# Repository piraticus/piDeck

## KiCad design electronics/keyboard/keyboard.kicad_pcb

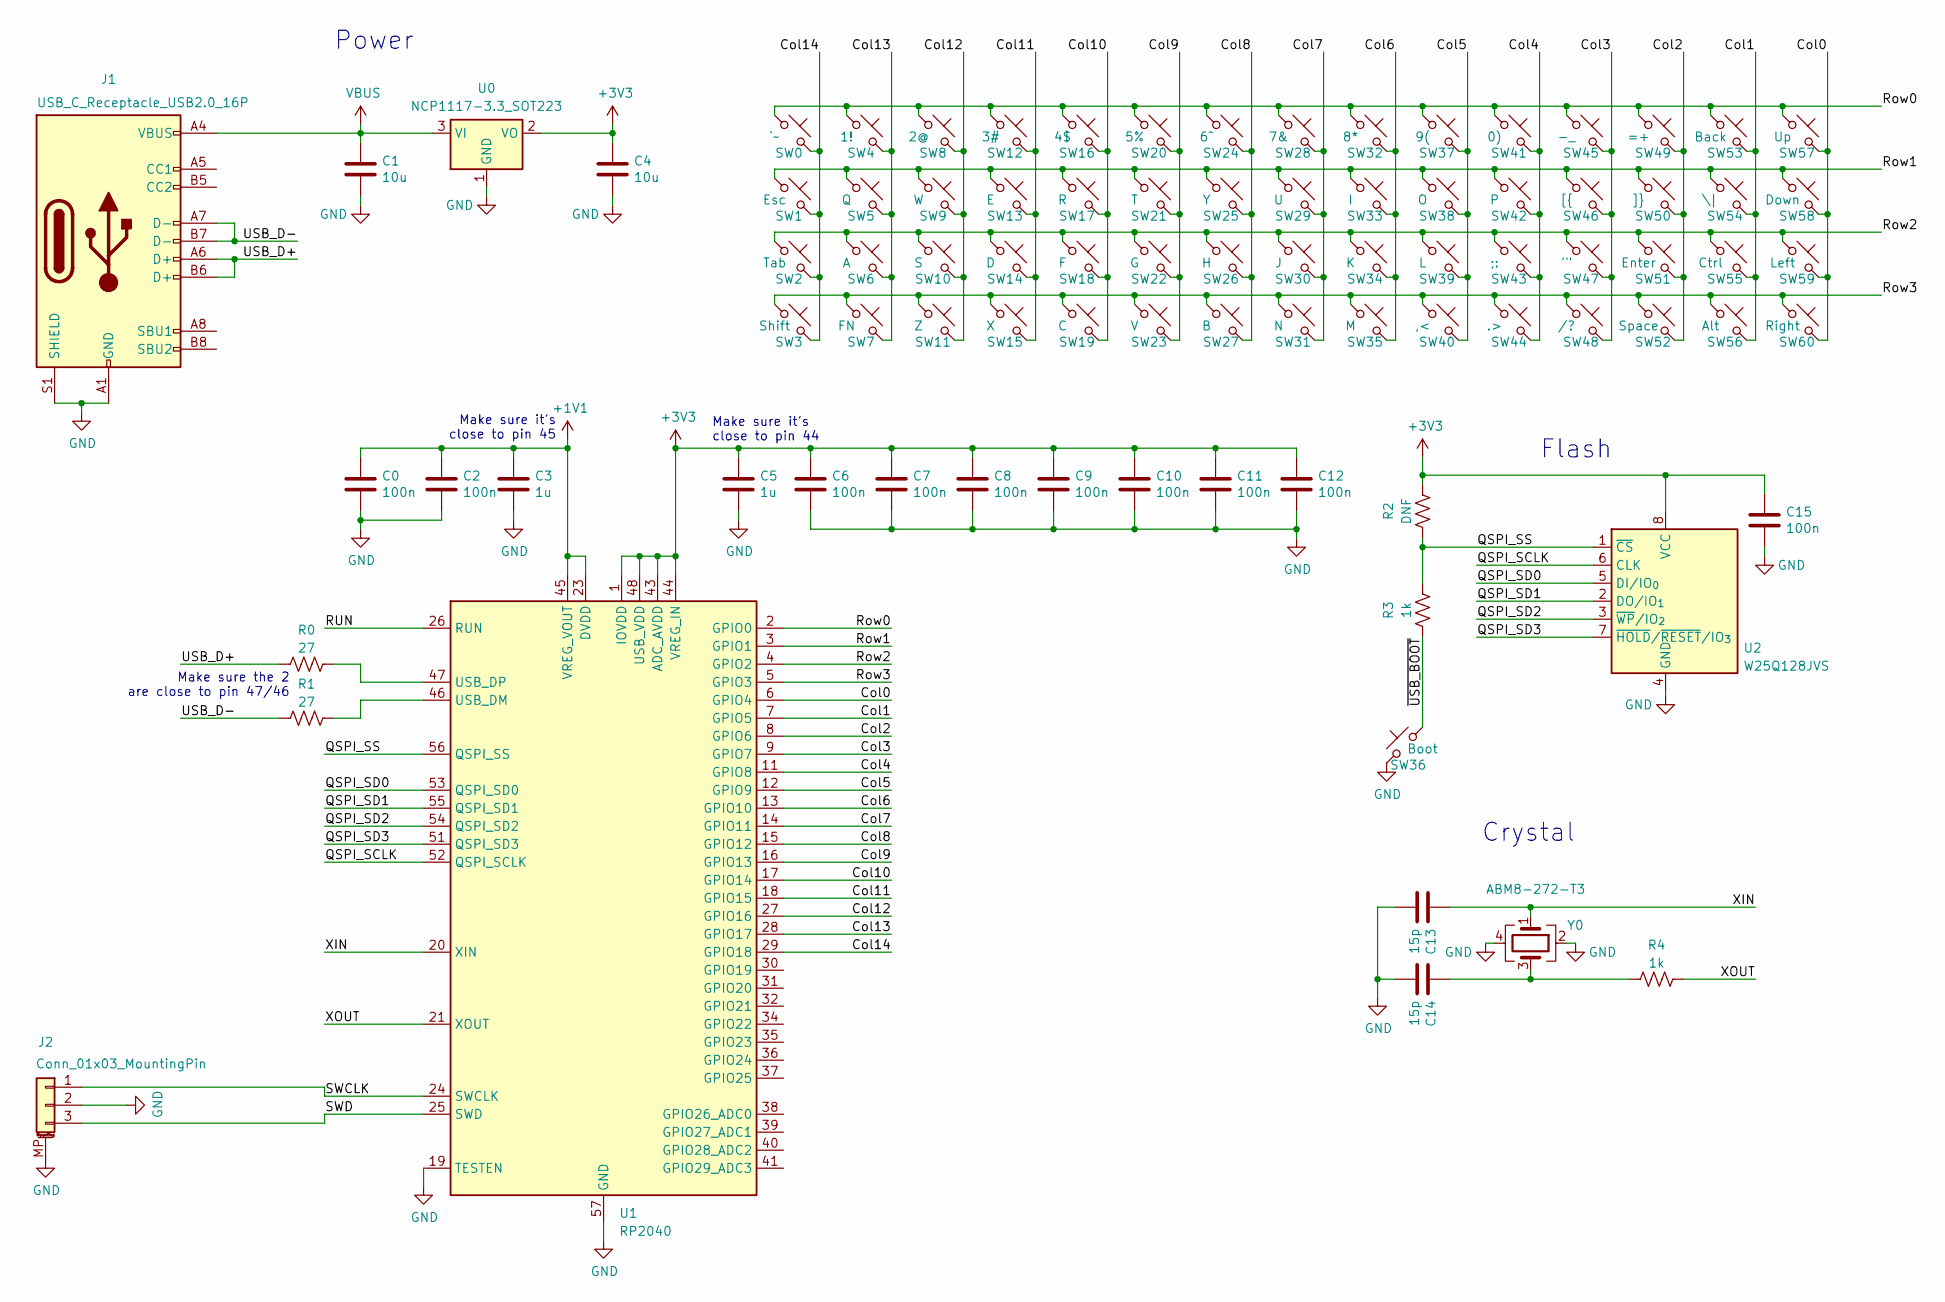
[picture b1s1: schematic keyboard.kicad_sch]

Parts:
C0, C2, C6, C7, C8, C9, C10, C11, C12, C15: 100n; C_0603_1608Metric_Pad1.08x0.95mm_HandSolder
C1, C4: 10u; C_0805_2012Metric_Pad1.18x1.45mm_HandSolder
C3, C5: 1u; C_0603_1608Metric_Pad1.08x0.95mm_HandSolder
C13, C14: 15p; C_0402_1005Metric_Pad0.74x0.62mm_HandSolder
J1: USB_C_Receptacle_USB2.0_16P; USB_C_Receptacle_GCT_USB4085
J2: Conn_01x03_MountingPin; JST_SH_SM03B-SRSS-TB_1x03-1MP_P1.00mm_Horizontal
R0, R1: 27; R_0603_1608Metric_Pad0.98x0.95mm_HandSolder
R2: DNF; R_0603_1608Metric_Pad0.98x0.95mm_HandSolder
R3, R4: 1k; R_0603_1608Metric_Pad0.98x0.95mm_HandSolder
SW0: `~; SW_PUSH_6mm_H9.5mm
SW1: Esc; SW_PUSH_6mm_H9.5mm
SW2: Tab; SW_PUSH_6mm_H9.5mm
SW3: Shift; SW_PUSH_6mm_H9.5mm
SW4: 1!; SW_PUSH_6mm_H9.5mm
SW5: Q; SW_PUSH_6mm_H9.5mm
SW6: A; SW_PUSH_6mm_H9.5mm
SW7: FN; SW_PUSH_6mm_H9.5mm
SW8: 2@; SW_PUSH_6mm_H9.5mm
SW9: W; SW_PUSH_6mm_H9.5mm
SW10: S; SW_PUSH_6mm_H9.5mm
SW11: Z; SW_PUSH_6mm_H9.5mm
SW12: 3#; SW_PUSH_6mm_H9.5mm
SW13: E; SW_PUSH_6mm_H9.5mm
SW14: D; SW_PUSH_6mm_H9.5mm
SW15: X; SW_PUSH_6mm_H9.5mm
SW16: 4$; SW_PUSH_6mm_H9.5mm
SW17: R; SW_PUSH_6mm_H9.5mm
SW18: F; SW_PUSH_6mm_H9.5mm
SW19: C; SW_PUSH_6mm_H9.5mm
SW20: 5%; SW_PUSH_6mm_H9.5mm
SW21: T; SW_PUSH_6mm_H9.5mm
SW22: G; SW_PUSH_6mm_H9.5mm
SW23: V; SW_PUSH_6mm_H9.5mm
SW24: 6^; SW_PUSH_6mm_H9.5mm
SW25: Y; SW_PUSH_6mm_H9.5mm
SW26: H; SW_PUSH_6mm_H9.5mm
SW27: B; SW_PUSH_6mm_H9.5mm
SW28: 7&; SW_PUSH_6mm_H9.5mm
SW29: U; SW_PUSH_6mm_H9.5mm
SW30: J; SW_PUSH_6mm_H9.5mm
SW31: N; SW_PUSH_6mm_H9.5mm
SW32: 8*; SW_PUSH_6mm_H9.5mm
SW33: I; SW_PUSH_6mm_H9.5mm
SW34: K; SW_PUSH_6mm_H9.5mm
SW35: M; SW_PUSH_6mm_H9.5mm
SW36: Boot; SW_PUSH_6mm_H9.5mm
SW37: 9(; SW_PUSH_6mm_H9.5mm
SW38: O; SW_PUSH_6mm_H9.5mm
SW39: L; SW_PUSH_6mm_H9.5mm
SW40: ,<; SW_PUSH_6mm_H9.5mm
SW41: 0); SW_PUSH_6mm_H9.5mm
SW42: P; SW_PUSH_6mm_H9.5mm
SW43: ;:; SW_PUSH_6mm_H9.5mm
SW44: .>; SW_PUSH_6mm_H9.5mm
SW45: -_; SW_PUSH_6mm_H9.5mm
SW46: [{; SW_PUSH_6mm_H9.5mm
SW47: '"; SW_PUSH_6mm_H9.5mm
SW48: /?; SW_PUSH_6mm_H9.5mm
SW49: =+; SW_PUSH_6mm_H9.5mm
SW50: ]}; SW_PUSH_6mm_H9.5mm
SW51: Enter; SW_PUSH_6mm_H9.5mm
SW52: Space; SW_PUSH_6mm_H9.5mm
SW53: Back; SW_PUSH_6mm_H9.5mm
SW54: \|; SW_PUSH_6mm_H9.5mm
SW55: Ctrl; SW_PUSH_6mm_H9.5mm
SW56: Alt; SW_PUSH_6mm_H9.5mm
SW57: Up; SW_PUSH_6mm_H9.5mm
SW58: Down; SW_PUSH_6mm_H9.5mm
SW59: Left; SW_PUSH_6mm_H9.5mm
SW60: Right; SW_PUSH_6mm_H9.5mm
U0: NCP1117-3.3_SOT223; SOT-223-3_TabPin2
U1: RP2040; QFN-56-1EP_7x7mm_P0.4mm_EP3.2x3.2mm
U2: W25Q128JVS; SOIC-8_5.3x5.3mm_P1.27mm
Y0: ABM8-272-T3; Crystal_SMD_3225-4Pin_3.2x2.5mm

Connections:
+1V1: C0.1, C2.1, C3.1, U1.23 (DVDD), U1.45 (VREG_VOUT), U1.50 (DVDD)
+3V3: C4.1, C5.1, C6.1, C7.1, C8.1, C9.1, C10.1, C11.1, C12.1, C15.1, R2.2, U0.2 (VO), U1.1 (IOVDD), U1.10 (IOVDD), U1.22 (IOVDD), U1.33 (IOVDD), U1.42 (IOVDD), U1.43 (ADC_AVDD), U1.44 (VREG_IN), U1.48 (USB_VDD), U1.49 (IOVDD), U2.8 (VCC)
/Col0: SW57.2, SW58.2, SW59.2, SW60.2, U1.6 (GPIO4)
/Col1: SW53.2, SW54.2, SW55.2, SW56.2, U1.7 (GPIO5)
/Col2: SW49.2, SW50.2, SW51.2, SW52.2, U1.8 (GPIO6)
/Col3: SW45.2, SW46.2, SW47.2, SW48.2, U1.9 (GPIO7)
/Col4: SW41.2, SW42.2, SW43.2, SW44.2, U1.11 (GPIO8)
/Col5: SW37.2, SW38.2, SW39.2, SW40.2, U1.12 (GPIO9)
/Col6: SW32.2, SW33.2, SW34.2, SW35.2, U1.13 (GPIO10)
/Col7: SW28.2, SW29.2, SW30.2, SW31.2, U1.14 (GPIO11)
/Col8: SW24.2, SW25.2, SW26.2, SW27.2, U1.15 (GPIO12)
/Col9: SW20.2, SW21.2, SW22.2, SW23.2, U1.16 (GPIO13)
/Col10: SW16.2, SW17.2, SW18.2, SW19.2, U1.17 (GPIO14)
/Col11: SW12.2, SW13.2, SW14.2, SW15.2, U1.18 (GPIO15)
/Col12: SW8.2, SW9.2, SW10.2, SW11.2, U1.27 (GPIO16)
/Col13: SW4.2, SW5.2, SW6.2, SW7.2, U1.28 (GPIO17)
/Col14: SW0.2, SW1.2, SW2.2, SW3.2, U1.29 (GPIO18)
/QSPI_SCLK: U1.52 (QSPI_SCLK), U2.6 (CLK)
/QSPI_SD0: U1.53 (QSPI_SD0), U2.5 (DI/IO_{0})
/QSPI_SD1: U1.55 (QSPI_SD1), U2.2 (DO/IO_{1})
/QSPI_SD2: U1.54 (QSPI_SD2), U2.3 (~WP/IO_{2})
/QSPI_SD3: U1.51 (QSPI_SD3), U2.7 (~HOLD/~RESET/IO_{3})
/QSPI_SS: R2.1, R3.2, U1.56 (QSPI_SS), U2.1 (~CS)
/RUN: U1.26 (RUN)
/Row0: SW0.1, SW4.1, SW8.1, SW12.1, SW16.1, SW20.1, SW24.1, SW28.1, SW32.1, SW37.1, SW41.1, SW45.1, SW49.1, SW53.1, SW57.1, U1.2 (GPIO0)
/Row1: SW1.1, SW5.1, SW9.1, SW13.1, SW17.1, SW21.1, SW25.1, SW29.1, SW33.1, SW38.1, SW42.1, SW46.1, SW50.1, SW54.1, SW58.1, U1.3 (GPIO1)
/Row2: SW2.1, SW6.1, SW10.1, SW14.1, SW18.1, SW22.1, SW26.1, SW30.1, SW34.1, SW39.1, SW43.1, SW47.1, SW51.1, SW55.1, SW59.1, U1.4 (GPIO2)
/Row3: SW3.1, SW7.1, SW11.1, SW15.1, SW19.1, SW23.1, SW27.1, SW31.1, SW35.1, SW40.1, SW44.1, SW48.1, SW52.1, SW56.1, SW60.1, U1.5 (GPIO3)
/SWCLK: J2.1, U1.24 (SWCLK)
/SWD: J2.3, U1.25 (SWD)
/USB_D+: J1.A6 (D+), J1.B6 (D+), R0.1
/USB_D-: J1.A7 (D-), J1.B7 (D-), R1.1
/XIN: C13.1, U1.20 (XIN), Y0.1
/XOUT: R4.2, U1.21 (XOUT)
/~USB_BOOT: R3.1, SW36.1
GND: C0.2, C1.2, C2.2, C3.2, C4.2, C5.2, C6.2, C7.2, C8.2, C9.2, C10.2, C11.2, C12.2, C13.2, C14.2, C15.2, J1.A1 (GND), J1.A12 (GND), J1.B1 (GND), J1.B12 (GND), J1.S1 (SHIELD), J2.2, J2.MP (MountPin), SW36.2, U0.1 (GND), U1.19 (TESTEN), U1.57 (GND), U2.4 (GND), Y0.2, Y0.4
unnamed: C14.1, R4.1, Y0.3
unnamed: R1.2, U1.46 (USB_DM)
unnamed: R0.2, U1.47 (USB_DP)
VBUS: C1.1, J1.A4 (VBUS), J1.A9 (VBUS), J1.B4 (VBUS), J1.B9 (VBUS), U0.3 (VI)

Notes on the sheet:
Make sure the 2 are close to pin 47/46
Flash
Power
Make sure it's close to pin 44
Make sure it's close to pin 45
Crystal

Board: 2 copper layers, 88 parts (0 on the bottom side), 39 nets, no tracks yet.

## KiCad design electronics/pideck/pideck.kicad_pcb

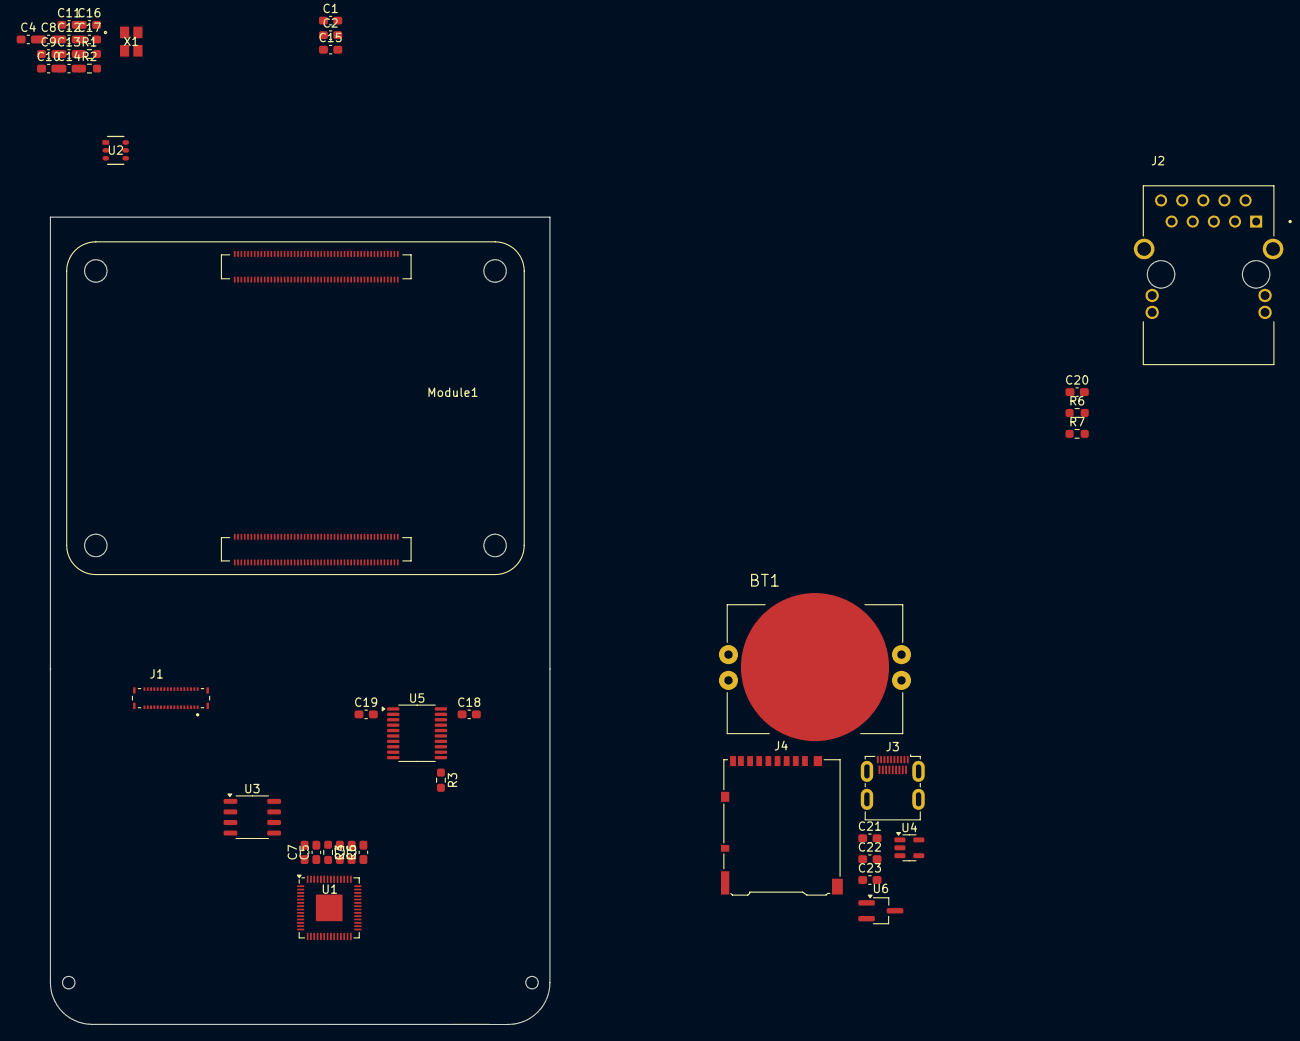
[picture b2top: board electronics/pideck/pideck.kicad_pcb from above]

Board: 2 copper layers, 60.1 x 97.1 mm, 43 parts (0 on the bottom side), 60 nets, no tracks yet.

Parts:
BT1: BAT-HLD-001-THM; BAT_BAT-HLD-001-THM
C1, C2, C3, C6, C15, C18, C19: 1uF; C_0603_1608Metric_Pad1.08x0.95mm_HandSolder
C4, C5, C7, C8, C9, C10, C11, C12, C13, C14, C20, C22, C23: 100nF; C_0603_1608Metric_Pad1.08x0.95mm_HandSolder
C16, C17: 15pF; C_0603_1608Metric_Pad1.08x0.95mm_HandSolder
C21: 10uF; C_0603_1608Metric_Pad1.08x0.95mm_HandSolder
J1: BM20B_0.8_-34DS-0.4V_53_; HIROSE_BM20B_0.8_-34DS-0.4V_53_
J2: ARJM11D7-502-AB-EW2; ABRACON_ARJM11D7-502-AB-EW2
J3: HDMI_D_1.4; HDMI_Micro-D_Molex_46765-1x01
J4: Micro_SD_Card_Det2; microSD_HC_Hirose_DM3AT-SF-PEJM5
Module1: ComputeModule5-CM5; Raspberry-Pi-5-Compute-Module
R1, R3: 10K; R_0603_1608Metric_Pad0.98x0.95mm_HandSolder
R2: 1k; R_0603_1608Metric_Pad0.98x0.95mm_HandSolder
R4, R5: 27.4k; R_0603_1608Metric_Pad0.98x0.95mm_HandSolder
R6, R7: 470; R_0603_1608Metric_Pad0.98x0.95mm_HandSolder
U1: RP2040; QFN-56-1EP_7x7mm_P0.4mm_EP3.2x3.2mm
U2: AP7312-1828W6-7; SOT26_DIO
U3: GD25Q16ETIGR; SOP-8_3.9x4.9mm_P1.27mm
U4: RT9742GGJ5; SOT-23-5
U5: TXS0108EPW; TSSOP-20_4.4x6.5mm_P0.65mm
U6: RT9742SNGV; TSOT-23_HandSoldering
X1: ABM8-272-T3; ABM8-272-T3_ABR

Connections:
+1V1: C3.1, C4.1, C5.1, U1.23 (DVDD), U1.45 (VREG_VOUT), U1.50 (DVDD)
+1V8: C2.2, C19.2, J1.26, R3.2, U2.6 (OUT1), U5.2 (VCCA), U5.10 (OE)
+2V8: C1.1, J1.30, U2.1 (OUT2)
+5V: C23.1, U6.1 (IN)
/+3v3: J2.P11, J2.P13
/QSPI_SCK: U1.52 (QSPI_SCLK), U3.6 (SCK)
/QSPI_SD0: U1.53 (QSPI_SD0), U3.5 (SI/IO0)
/QSPI_SD1: U1.55 (QSPI_SD1), U3.2 (SO/IO1)
/QSPI_SD2: U1.54 (QSPI_SD2), U3.3 (~WP/IO2)
/QSPI_SD3: U1.51 (QSPI_SD3), U3.7 (~HOLD/IO3)
/~QSPI_CS: R1.2, U1.56 (QSPI_SS), U3.1 (~CS)
ETH_LEDG: Module1.17 (Ethernet_nLED2(3.3v)), R6.1
ETH_LEDY: Module1.15 (Ethernet_nLED3(3.3v)), R7.1
GND: C1.2, C2.1, C3.2, C4.2, C5.2, C6.2, C7.2, C8.2, C9.2, C10.2, C11.2, C12.2, C13.2, C14.2, C15.1, C16.1, C17.2, C18.2, C19.1, C20.2, C21.2, C22.2, C23.2, J1.1, J1.2, J1.33, J1.34, J2.S1 (SHIELD), J2.S2 (SHIELD__1), J3.4 (D2S), J3.7 (D1S), J3.10 (D0S), J3.13 (CKS), J3.16 (GND), J3.SH, J4.6 (VSS), J4.11 (SHIELD), R3.1, U2.2 (GND), U3.4 (GND), U4.2 (GND), U5.11 (GND), U6.3 (GND), X1.2, X1.4
HDMI0_CEC: J3.15 (CEC), Module1.151 (HDMI0_CEC)
HDMI0_D0_N: J3.11 (D0-), Module1.184 (HDMI0_TX0_N)
HDMI0_D0_P: J3.9 (D0+), Module1.182 (HDMI0_TX0_P)
HDMI0_D1_N: J3.8 (D1-), Module1.178 (HDMI0_TX1_N)
HDMI0_D1_P: J3.6 (D1+), Module1.176 (HDMI0_TX1_P)
HDMI0_D2_N: J3.5 (D2-), Module1.172 (HDMI0_TX2_N)
HDMI0_D2_P: J3.3 (D2+), Module1.170 (HDMI0_TX2_P)
HDMI0_HOTPLUG: J3.1 (HPD/HEAC-), Module1.153 (HDMI0_HOTPLUG)
HDMI0_SCL: J3.17 (SCL), Module1.200 (HDMI0_SCL)
HDMI0_SDA: J3.18 (SDA), Module1.199 (HDMI0_SDA)
HDMI_5v: C22.1, J3.19 (+5V), U6.2 (OUT)
KB_BLK_LED_A: C6.1, C7.1, C8.1, C9.1, C10.1, C11.1, C12.1, C13.1, C14.1, C15.2, C18.1, J1.17, J1.19, R1.1, U1.1 (IOVDD), U1.10 (IOVDD), U1.22 (IOVDD), U1.33 (IOVDD), U1.42 (IOVDD), U1.43 (ADC_AVDD), U1.44 (VREG_IN), U1.48 (USB_VDD), U1.49 (IOVDD), U2.3 (EN2), U2.4 (EN1), U2.5 (IN), U3.8 (VDD), U4.5 (IN), U5.19 (VCCB)
KB_BLK_LED_K_1V8: J1.21, J1.23, J1.25, J1.27, U5.1 (A1)
KB_USB_D+: Module1.105 (USB2_P), R4.1
KB_USB_D-: Module1.103 (USB2_N), R5.1
unnamed: BT1.N, Module1.74 (GND)
unnamed: C17.1, R2.1, X1.3
unnamed: C20.1, J2.P5 (CT_1), J2.P6 (CT_2)
unnamed: J2.P12, R6.2
unnamed: J2.P14, R7.2
unnamed: BT1.P1, BT1.P2, BT1.P3, BT1.P4, Module1.76 (VBAT)
unnamed: R5.2, U1.46 (USB_DM)
unnamed: R4.2, U1.47 (USB_DP)
unnamed: C16.2, U1.20 (XIN), X1.1
unnamed: R2.2, U1.21 (XOUT)
PANNEL_BLK_LED_K_1V8: J1.29, J1.31, U5.3 (A2)
SD_DAT0: J4.7 (DAT0), Module1.63 (SD_DAT0)
SD_DAT1: J4.8 (DAT1), Module1.67 (SD_DAT1)
SD_DAT2: J4.1 (DAT2), Module1.69 (SD_DAT2)
SD_DAT3: J4.2 (DAT3/CD), Module1.61 (SD_DAT3)
SD_PWR: C21.1, J4.4 (VDD), U4.1 (OUT)
SD_PWR_ON: Module1.75 (SD_PWR_ON), U4.4 (EN)
TP_BLK_LED_K_1V8: J1.28, U5.6 (A5)
TP_MOTION_1V8: J1.18, U5.4 (A3)
TP_RESET_1V8: J1.32, U5.5 (A4)
TP_SCL_1V8: J1.22, U5.8 (A7)
TP_SDA_1V8: J1.24, U5.9 (A8)
TP_SHUTDOWN_1V8: J1.20, U5.7 (A6)
TRD0_N: J2.P2 (TD1-), Module1.12 (Ethernet_Pair0_P)
TRD0_P: J2.P1 (TD1+), Module1.10 (Ethernet_Pair0_N)
TRD1_N: J2.P4 (TD2-), Module1.6 (Ethernet_Pair1_N)
TRD1_P: J2.P3 (TD2+), Module1.4 (Ethernet_Pair1_P)
TRD2_N: J2.P8 (TD3-), Module1.9 (Ethernet_Pair2_N)
TRD2_P: J2.P7 (TD3+), Module1.11 (Ethernet_Pair2_P)
TRD3_N: J2.P10 (TD4-), Module1.3 (Ethernet_Pair3_P)
TRD3_P: J2.P9 (TD4+), Module1.5 (Ethernet_Pair3_N)

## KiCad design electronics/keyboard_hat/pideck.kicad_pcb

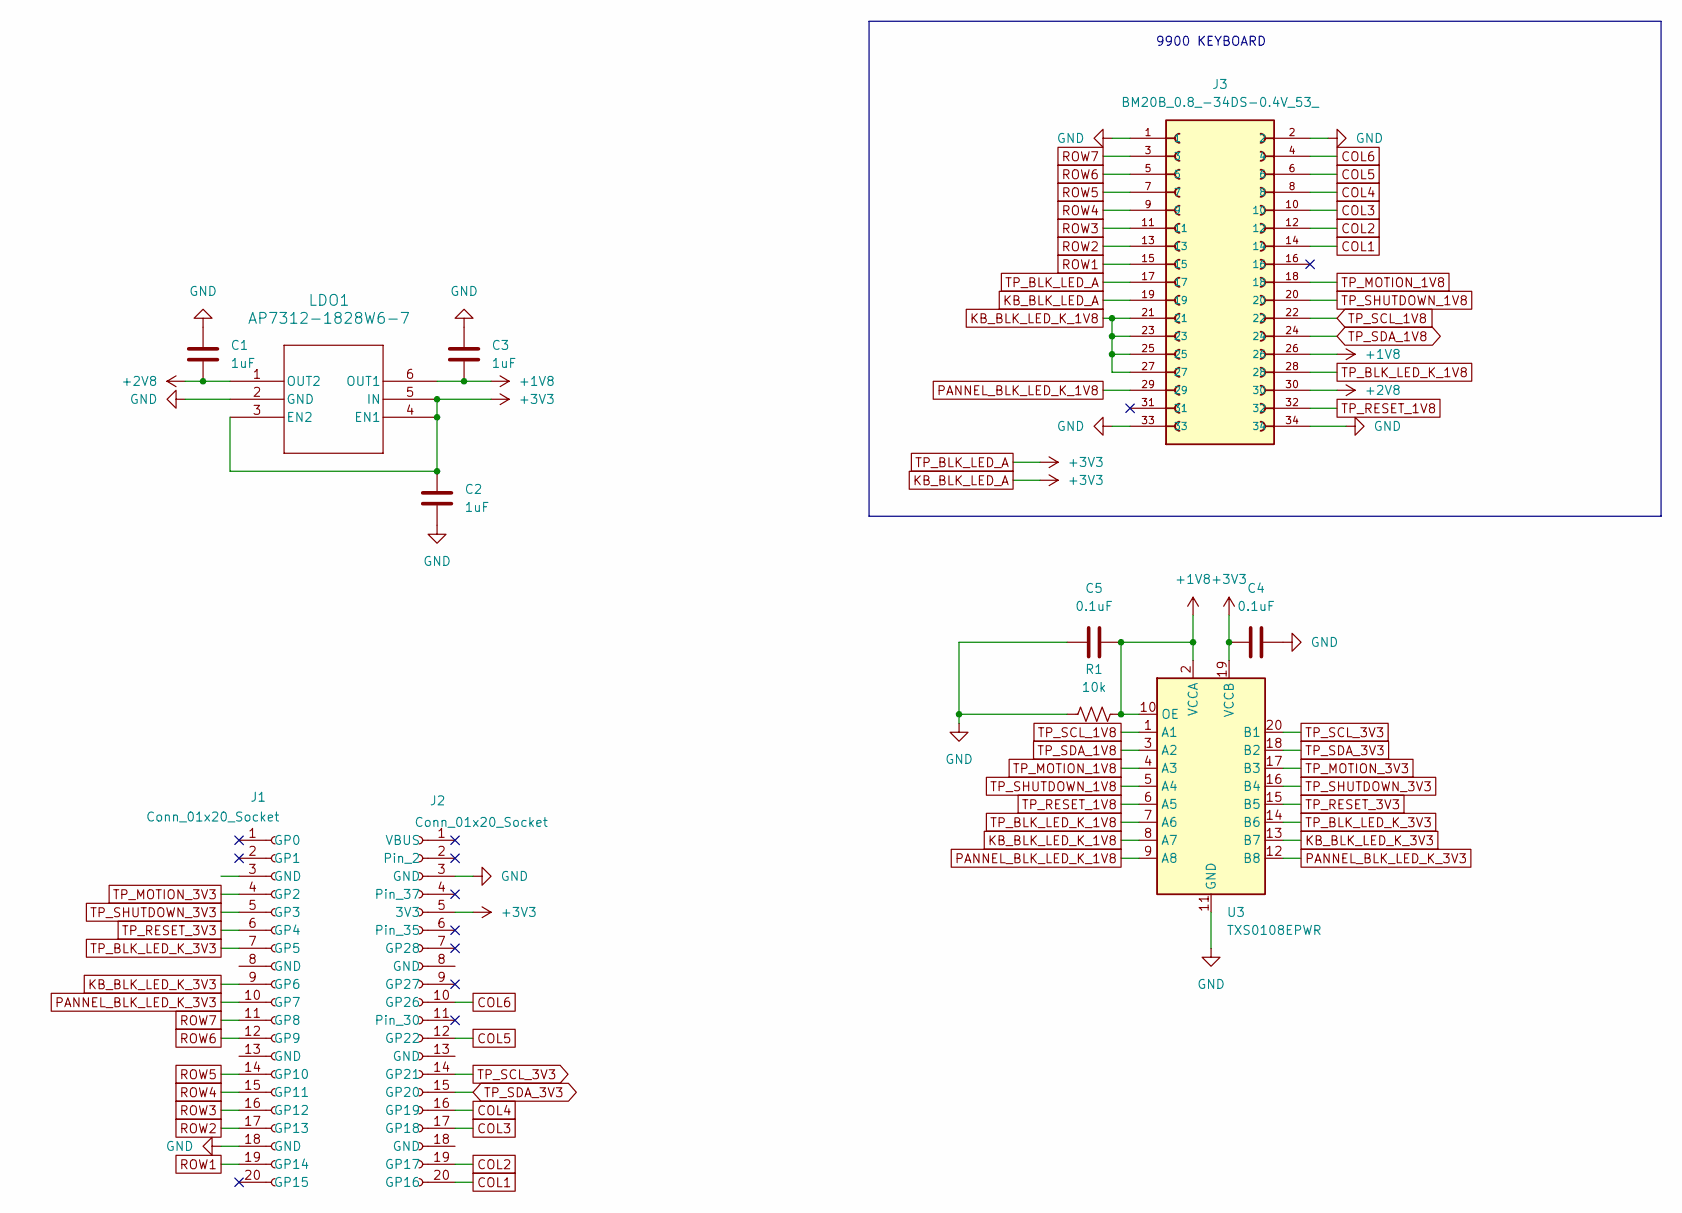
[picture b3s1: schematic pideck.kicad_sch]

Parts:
C1, C2, C3: 1uF; C_0603_1608Metric
C4, C5: 0.1uF; C_0603_1608Metric
J1, J2: Conn_01x20_Socket; PinSocket_1x20_P2.54mm_Vertical
J3: BM20B_0.8_-34DS-0.4V_53_; HIROSE_BM20B_0.8_-34DS-0.4V_53_; PARTREV 0
LDO1: AP7312-1828W6-7; SOT26_DIO
R1: 10k; R_0603_1608Metric
U3: TXS0108EPWR; TSSOP-20_4.4x6.5mm_P0.65mm

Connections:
+1V8: C3.2, C5.2, J3.26, LDO1.6 (OUT1), R1.2, U3.2 (VCCA), U3.10 (OE)
+2V8: C1.2, J3.30, LDO1.1 (OUT2)
COL1: J2.20 (GP16), J3.14
COL2: J2.19 (GP17), J3.12
COL3: J2.17 (GP18), J3.10
COL4: J2.16 (GP19), J3.8
COL5: J2.12 (GP22), J3.6
COL6: J2.10 (GP26), J3.4
GND: C1.1, C2.2, C3.1, C4.2, C5.1, J1.18 (GND), J2.3 (GND), J3.1, J3.2, J3.33, J3.34, LDO1.2 (GND), R1.1, U3.11 (GND)
KB_BLK_LED_A: C2.1, C4.1, J2.5 (3V3), J3.17, J3.19, LDO1.3 (EN2), LDO1.4 (EN1), LDO1.5 (IN), U3.19 (VCCB)
KB_BLK_LED_K_1V8: J3.21, J3.23, J3.25, J3.27, U3.8 (A7)
KB_BLK_LED_K_3V3: J1.9 (GP6), U3.13 (B7)
PANNEL_BLK_LED_K_1V8: J3.29, U3.9 (A8)
PANNEL_BLK_LED_K_3V3: J1.10 (GP7), U3.12 (B8)
ROW1: J1.19 (GP14), J3.15
ROW2: J1.17 (GP13), J3.13
ROW3: J1.16 (GP12), J3.11
ROW4: J1.15 (GP11), J3.9
ROW5: J1.14 (GP10), J3.7
ROW6: J1.12 (GP9), J3.5
ROW7: J1.11 (GP8), J3.3
TP_BLK_LED_K_1V8: J3.28, U3.7 (A6)
TP_BLK_LED_K_3V3: J1.7 (GP5), U3.14 (B6)
TP_MOTION_1V8: J3.18, U3.4 (A3)
TP_MOTION_3V3: J1.4 (GP2), U3.17 (B3)
TP_RESET_1V8: J3.32, U3.6 (A5)
TP_RESET_3V3: J1.6 (GP4), U3.15 (B5)
TP_SCL_1V8: J3.22, U3.1 (A1)
TP_SCL_3V3: J2.14 (GP21), U3.20 (B1)
TP_SDA_1V8: J3.24, U3.3 (A2)
TP_SDA_3V3: J2.15 (GP20), U3.18 (B2)
TP_SHUTDOWN_1V8: J3.20, U3.5 (A4)
TP_SHUTDOWN_3V3: J1.5 (GP3), U3.16 (B4)

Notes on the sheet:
9900 KEYBOARD

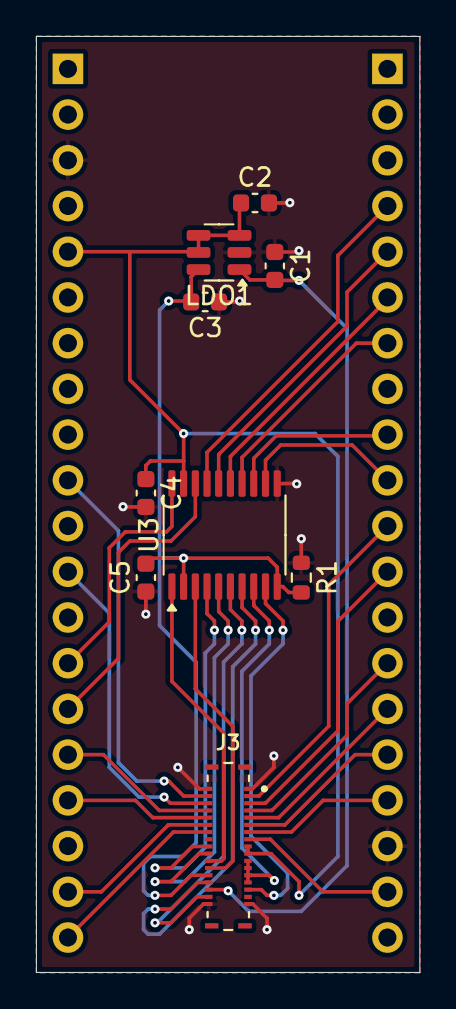
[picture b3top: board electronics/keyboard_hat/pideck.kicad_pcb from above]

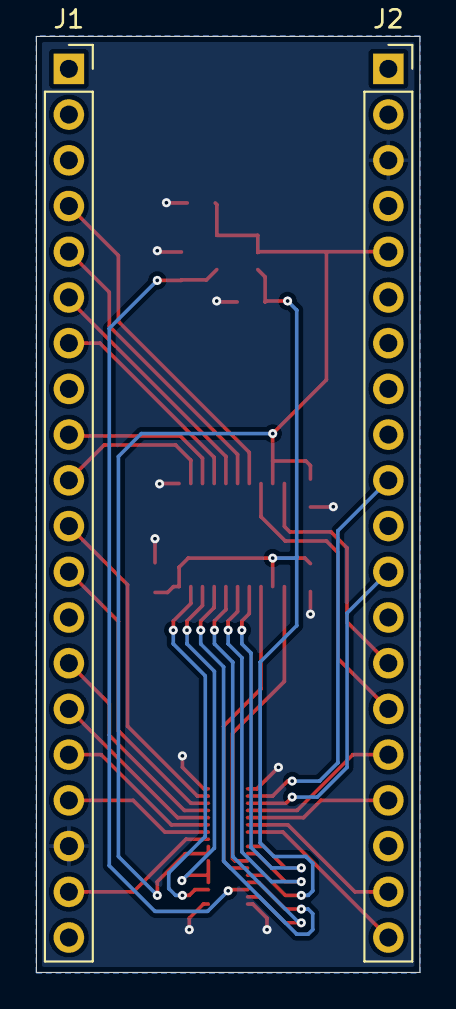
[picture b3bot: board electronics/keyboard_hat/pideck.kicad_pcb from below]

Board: 2 copper layers, 21.3 x 52.0 mm, 11 parts (2 on the bottom side), 33 nets.

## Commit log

2025-03-27 work in progress schematics
2025-04-01 schematics complete
2025-04-02 routed
2025-04-09 new routing
2025-04-09 updatign project file
2025-05-06 finished hat and started full deck
2025-05-15 updated schematic to new chip and completed layout
2025-05-22 updating gitignore
2025-05-22 Adding ethernet, hdmi, and battery to CM5
2025-05-22 remove ds_ignore
2025-05-24 added usb
2025-06-10 adding component docs
2025-06-10 started the diagram
2025-06-23 simple keyboard initial layout
2025-07-11 updating schematic of the keyboard
